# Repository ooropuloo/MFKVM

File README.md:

# MF KVM

**繁體中文** | [English](README.en.md)

MF KVM 是以 ESP32-P4 為主控、跑 [ESP-KVM](https://github.com/espkvm/espkvm) 韌體的 KVM over IP 小盒子：接上主機的 HDMI 和 USB 之後，就能透過 Wi-Fi 從瀏覽器看主機畫面、操作鍵盤滑鼠，也能按主機的電源和重置鍵。這個 repo 並列兩個設計：`off-the-shelf/` 用買得到的現成板組裝，只自製一片 ATX 小板；`lay-board/` 把所有電路自己布在一片 6 層板上。

**狀態：還沒有做出實品。** 目前版本 r7f 已送 JLC 審核、尚未付款。通過的都是檔案和模型層級的檢查，沒有任何一項在硬體上驗證過。

授權見 [LICENSE](LICENSE)：硬體 CERN-OHL-P-2.0、程式 Apache-2.0、文件 CC-BY-4.0。第三方內容另依原本的條款，見 [THIRD_PARTY.md](THIRD_PARTY.md)。

## 目前版本：r7f

6 層單片板，雙面放零件。主控是 ESP32-P4-Module（U1，組裝後手焊），影像用 TC358743（U7，BGA）。

| 正面 | 背面 |
|---|---|
|  |  |

<details>
<summary>零件代號對照表（點開看圖查詢）</summary>

**正面（Top）**

| 代號 | 是什麼 | 用途／備註 |
|---|---|---|
| U1 | ESP32-P4 模組 | 主控加 Wi-Fi，客供、組裝後手焊，最大熱源 |
| J3 | USB-C | 接被控主機（鍵盤滑鼠、虛擬媒體） |
| J5 | USB-C | 5 V 供電、燒錄、console |
| J6 | SM08B 8P | 接圓形 LCD |
| U14 | ESD 保護 | J5 的 USB 線 |
| U15 + L2 | 降壓 | 3V3 → 1.2 V |
| D1 | ESD 保護 | HDMI CEC |

**背面（Bottom）**

| 代號 | 是什麼 | 用途／備註 |
|---|---|---|
| J2 | HDMI | 影像輸入 |
| U7 | TC358743 BGA | HDMI 轉 CSI，最燙的晶片 |
| J7 | microSD | 虛擬媒體、儲存 |
| U16 | TPS259531 eFuse | 5 V 輸入保護，下單要核對方向 |
| U2 + L1 | 降壓 | 5 V → 3V3 |
| U4 | LDO | 3V3 → 2.5 V |
| U6 | TCA9517A | HDMI DDC 準位轉換 |
| U3、U8、U9 | ESD 保護 | J3 的 USB 線、HDMI TMDS |
| U10、U11、U12 | 光耦 | ATX 電源、重置、LED |
| J4 | SM06B 6P | 接 ATX 前面板 |
| J8 | U.FL | 接 Wi-Fi 天線 |
| Y1 | 27 MHz 振盪器 | U7 的時脈 |
| Q1 | P 通道 MOSFET | microSD 電源開關 |
| C69 | 330 µF POSCAP | 5 V 大電容 |

電阻、電容太多沒有列，完整清單見 [`BOM_JLC.csv`](lay-board/r7f/fab_r7f/BOM_JLC.csv)。

</details>

| 外殼組裝 | 爆炸圖 |
|---|---|
|  |  |

以上都是電腦算繪，不是照片。板檔沒有 3D 模型，零件是依外形和高度畫的方塊，風扇是示意外形。

| 項目 | 規格 |
|---|---|
| 板子 | 40 × 45 mm，6 層，JLC06121H-3313 |
| 外殼本體 | 44 × 49 × 20 mm，鋁上蓋，底殼 ASA／ABS／PC／PA12（不用 PLA） |
| 含導管和風扇 | 44 × 69.2 × 35 mm（風扇厚度 10 mm 是假設） |
| 額定環境溫度 | 25 °C，要裝導管式風扇 |
| 主控 | ESP32-P4-Module 基本款（SKU 28101），內建 ESP32-C6，2.4 GHz Wi-Fi，U.FL 外接天線 |
| 影像 | TC358743XBG，HDMI 轉 CSI |
| 螢幕 | 1.28 吋圓形 LCD |
| 打板包 | [`lay-board/r7f/fab_r7f/`](lay-board/r7f/fab_r7f/)，Gerber zip sha256 開頭 `5edbd116` |

### 這版改了什麼（相對 r7e）

下表的數字都是模型算出來的，不是實測。

| 項目 | 改了什麼 | 結果 |
|---|---|---|
| 5 V 輸入保護 | 加 eFuse U16（TPS259531），限流約 2 A，輸出鉗位 5.7 V | 插電瞬間峰值電流 10–18 A → 4.1–5.3 A |
| HDMI CEC | CEC 線加 ESD 保護 D1（TPD1E10B06） | 原本這條線沒有保護 |
| microSD 訊號 | 6 條線各串 22 Ω（R74–R79） | 寫入過衝 0.79–1.16 V → 0.05–0.23 V |
| LCD 訊號 | DIN、CLK 串 33 Ω（R80、R81，0201） | LCD CLK 過衝 1.51 V → 0.61 V |
| 散熱 | 鋁上蓋、0.8 mm 鋁板、P4 和 C6 上的導熱膠、12 條通風槽 | 一般負載下上蓋 52.9 °C → 49.5 °C（環境 25 °C） |
| 導管式風扇 | 加 3D 列印導管和 30 mm 風扇，風扇自己接 USB 供電，PCB 不改 | 上蓋 36.2 °C、底殼 41.5 °C，低於接觸超過 1 分鐘的 48 °C（0.15 L/s，流量是假設） |
| 外殼接地 | 安裝孔鍍通接地，上蓋和鋁板的接觸面不上陽極膜 | 驗收：上蓋、鋁板對 GND 要 < 1 Ω |
| 手焊間距 | U1 旁 22 個焊盤都留 ≥ 0.2 mm 和防焊隔開，J6 外移 0.65 mm | 最小 0.387 mm |

**從 r5 走到 r7f 的主要變化：** r6 加 U.FL 和 50 Ω RF 線、阻抗改用場解算；r7 的 1.2 V 改成降壓（U15）、DDC 改 TCA9517A；r7c 板子加長到 40 × 45 mm 並加 C69；r7d 做 CSI 等長；r7e 補冷啟動分析。

### 驗證到哪裡

| 已通過（檔案和模型層級） | 結果 |
|---|---|
| ERC、DRC | 0 錯誤、0 未連線，29 個警告逐項接受 |
| 電氣規則檢查（含 eFuse） | 全部通過 |
| 故意放錯測試 | 126 次全部抓到 |
| 外殼幾何 | 99/99 |
| 阻抗、CSI 等長、參考層、防焊、孔距、零件本體 | 通過 |
| 獨立複審與差異複審 | 0 嚴重，有條件可送板 |

**沒有驗證：** 還沒有實體板，EMI、RF／RSSI、影像、USB、Wi-Fi、風扇實際風量和溫度都沒測過。完整清單在[驗證報告](lay-board/r7f/pdf/r7f_驗證報告.pdf)第 2 節。

**現在的進度：** 已送 JLC 審核，尚未付款，尚未打板。JLC 按確認前還要在預覽逐顆核對 U16 第 1 腳和 16 顆方向未定的零件（U16 轉 180° 會讓 VBUS 短路到 GND）。

**完整資料：** [r7f 說明](lay-board/r7f/README.md)、[改版報告](lay-board/r7f/R7F_REPORT.md)、[獨立複審](lay-board/r7f/REVIEW_r7f.md)、[差異複審](lay-board/r7f/DELTA_r7f.md)、[圖面與報告 PDF](lay-board/r7f/pdf/)。

## 較早的設計（ARCHIVE）

以下保留當時的內容當紀錄，都不是目前版本。`lay-board/` 這欄是 r5，那張單已經取消。

| | [`off-the-shelf/`](off-the-shelf/README.md)（現成料，第三版） | [`lay-board/`](lay-board/README.md)（客製板，第二版 r5） |
|---|---|---|
| **外殼尺寸** | 75.0 × 38.05 × 26.73 mm | 44 × 44 × 20 mm |
| **體積** | 76 cm³ | 39 cm³ |
| **買什麼** | DFRobot FireBeetle 2 ESP32-P4（DFR1172）、Geekworm C790、Waveshare 1.9 吋 LCD、Würth 50 mm 15-pin 排線（接點異面、同面各 1）、改過不接 VBUS 的 USB 線、Ø0.64 銅線、JST SH 線、螺絲、5 V 電源 | Waveshare ESP32-P4-Module-U（IPEX）、FPC 天線、1.28 吋圓形 LCD、自製 SHR-08 和 SHR-06 線、M2 × 16 螺絲 4 支 |
| **打什麼板** | 2 層 ATX 小板 rev B，11.05 × 35.4 mm（`fab_atx_b/`），尚未下單 | 6 層 40 × 40 mm 主板加雙面 PCBA，含 BGA（`fab_r5/`），JLC 審查中、未付款 |
| **印什麼** | 底殼、上蓋、C790 橋架、排線捲線棒、ATX 焊接墊片（建議 PETG） | 底殼、上蓋 |
| **韌體** | ESP-KVM `0893eef`，加 ST7789 修補與 ATX 修補（兩支 patch），只編譯過 | ESP-KVM `0893eef`，加開機預設值修補與 ATX 修補（兩支 patch），只編譯過。ATX 預設關閉，到 console 打開，見 `lay-board/firmware/BUILD_v2.md` |
| **主要風險** | 排線斜捲 45° 沒人測過、回報僅約 9 fps、ATX 小板焊死後要斜著裝 | 首版 6 層加 BGA 有錯就要重打、阻抗只有公式估算、最壞公差有 4 對本體可能相碰 |
| **狀態** | 只有設計，零件未買 | 打板包只能送 CAM 預審，還不能算放行 |
| **什麼時候選它** | 想先驗證功能、不想打 6 層板和焊 BGA、接受比較大的盒子。目前建議當驗證機，也能先驗證兩邊共用的韌體 | 要最小的外形，或要走正式小型產品，且願意承擔首版改板 |

每個設計的 README 都有 **「還缺什麼」** 清單，列出下單前和實機要做的事：[off-the-shelf](off-the-shelf/README.md#還缺什麼)、[lay-board](lay-board/README.md#還缺什麼)。

## 當時的建議順序（r5 時期）

1. 買 `off-the-shelf` 的料，先用線接起來跑通影像、USB、Wi-Fi，不用打板也不用列印。
2. 拿實測影格率決定 `off-the-shelf` 能不能接受，同時驗證 `lay-board` 也會用到的韌體路徑。
3. `lay-board` 依 CAM 回覆決定要不要修，審查通過也先不付款，全部驗證過才打板。

## 3D 頁面

這兩個連結是**擁有者私人頁面，別人打不開**。每個資料夾裡的本機 HTML 是同一份內容，下載後用瀏覽器開就能看（3D 需要連上網路載入 three.js）：

| 設計 | 私人連結 | 本機檔案 |
|---|---|---|
| lay-board | https://claude.ai/artifact/GMou6HJAjchfPkJ2fzq8we | [`lay-board/kvm-mini.html`](lay-board/kvm-mini.html) |
| off-the-shelf | https://claude.ai/artifact/LdwRVth9BPiBVDjdgMhgdb | [`off-the-shelf/v3.html`](off-the-shelf/v3.html) |

## 不在這個 repo 的東西

- **第一版（NANO 模組疊自製底板）：** 排針位置錯，已放棄，沒有放進來。
- **舊打板包：** `fab`、`fab_new`、`fab_r2`～`fab_r4`、`fab_atx` 都不能用，原因寫在各 README。
- **建置輸出：** ESP-KVM clone、build 目錄、映像檔、建置 log。重新編譯的方法在各 README。
- **第三方原始檔：** NANO 官方 CAD、ExoAnchor 壓縮檔、FireBeetle STEP。來源見 [THIRD_PARTY.md](THIRD_PARTY.md) 和 `off-the-shelf/research/`。

## 常用檢查（在 repo 根目錄）

```sh
python lay-board/tools/maskcheck.py lay-board/fab_r5/p4_kvm_mini_gerber.zip
python lay-board/tools/holecheck.py lay-board/fab_r5/p4_kvm_mini_gerber.zip
sh lay-board/tools/check.sh out/final.ses     # 要 KiCad，路徑用 KICAD_CLI、KICAD_TOOL_HOME 覆寫
python lay-board/tools/bodycheck.py lay-board/out
python lay-board/tools/maskcheck.py off-the-shelf/fab_atx_b/mf_kvm_atx_gerber.zip
python lay-board/tools/holecheck.py off-the-shelf/fab_atx_b/mf_kvm_atx_gerber.zip
```

`.gitattributes` 設定 `* -text`，檔案逐位元組保存，不轉換行尾，所以 Gerber 雜湊不會變，`.sh` 也不會變成 CRLF。

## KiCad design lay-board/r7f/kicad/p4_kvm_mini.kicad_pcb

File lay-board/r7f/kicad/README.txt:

r7b design files, copied from out/ after the final check (board sha256 2acf1c0fcd2acbffd97f6878b55f344319c8f6496172503f295ab0cfc3b03e46).
They are the files fab_r7b/ was made from. Regenerate with gen_mini.py; do not edit these by hand.

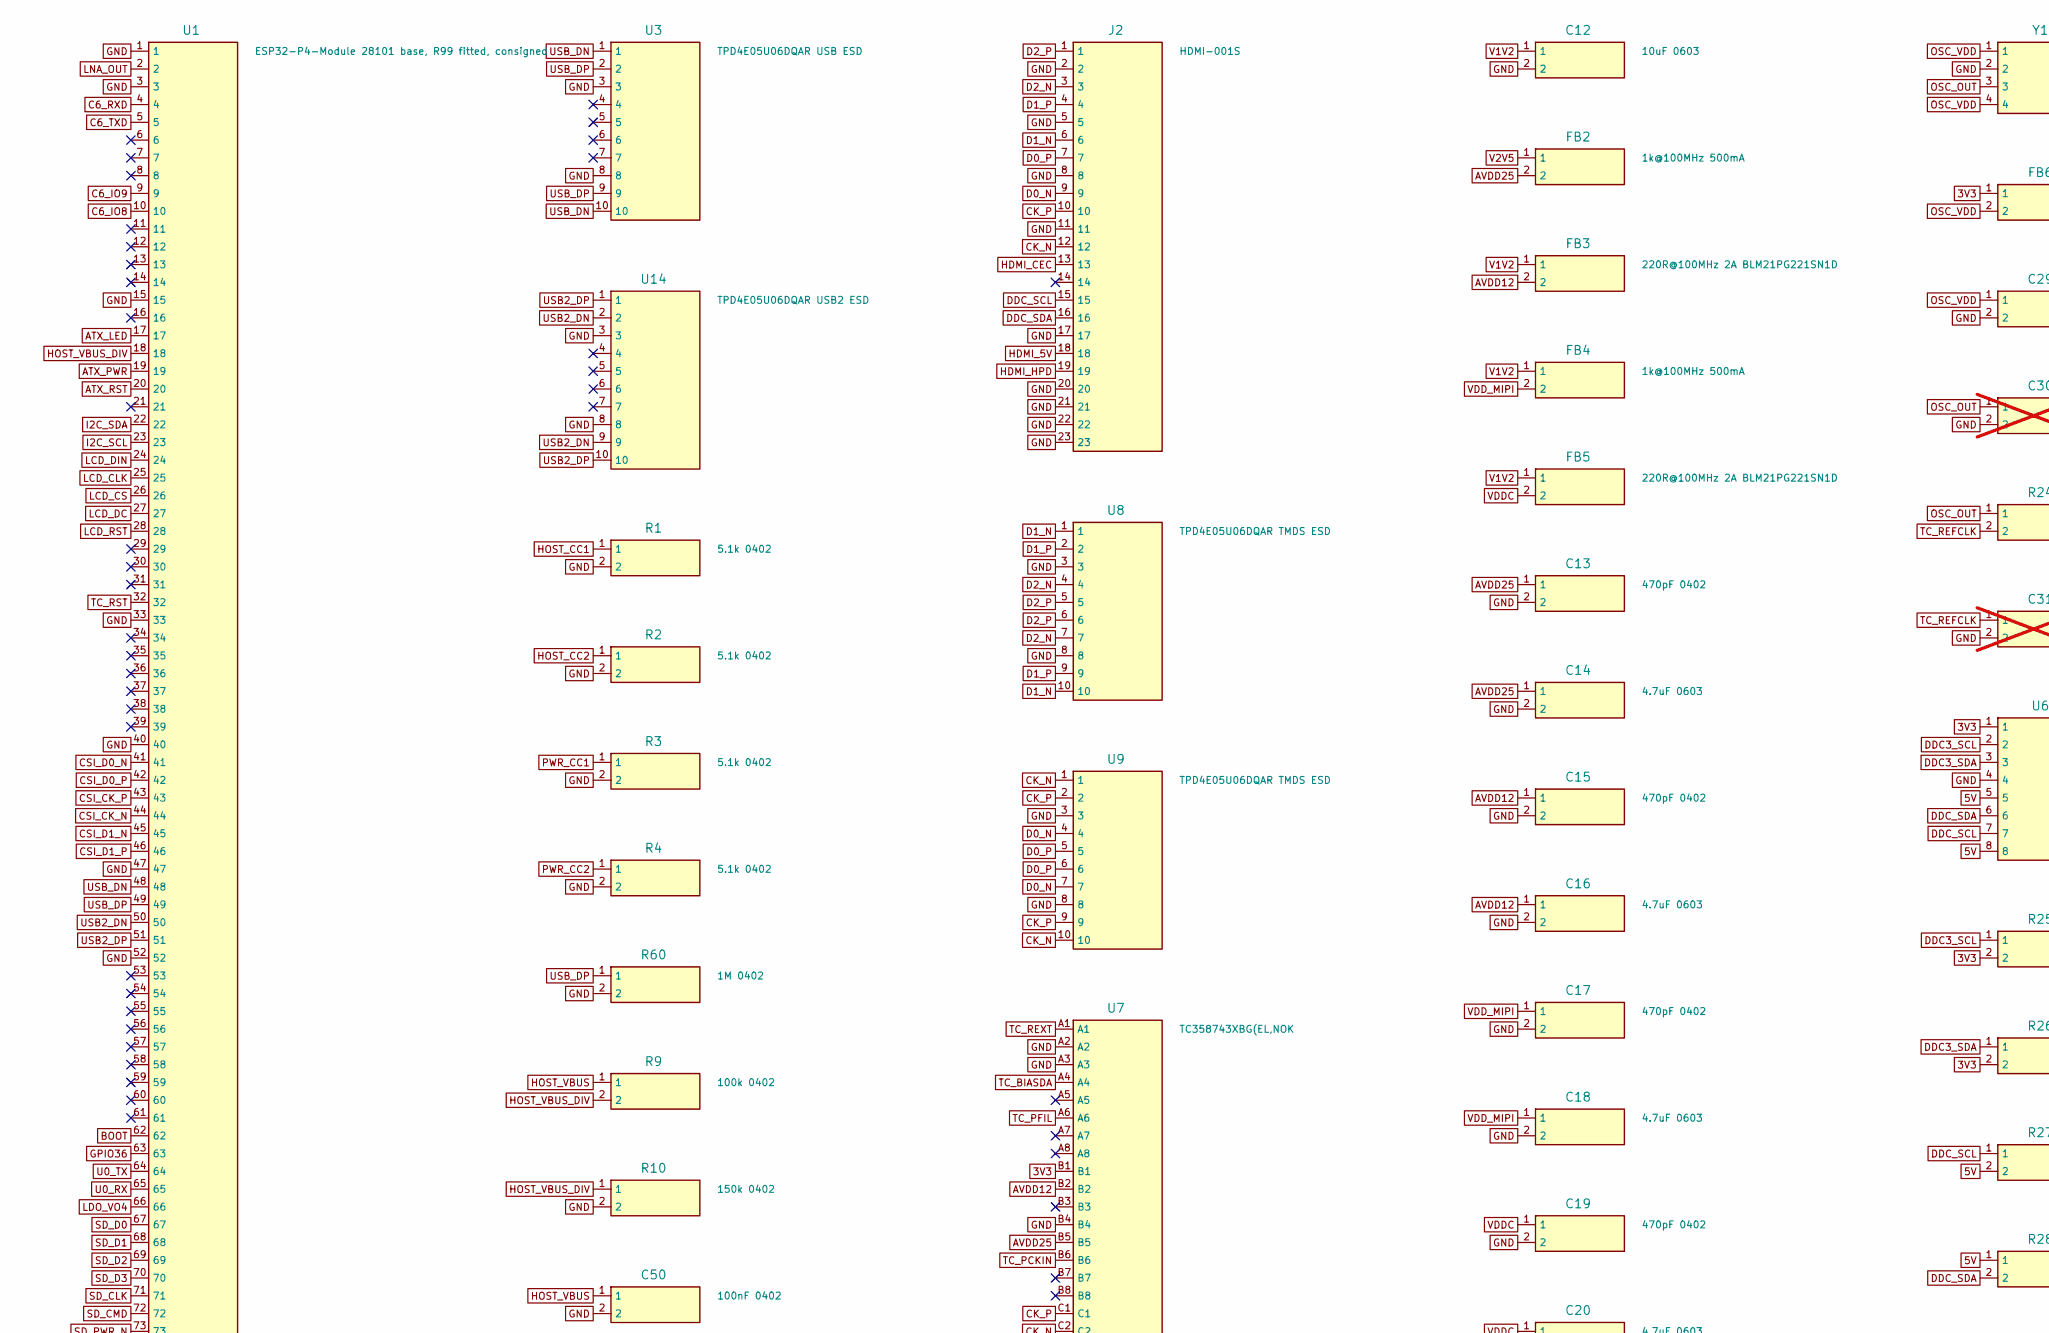
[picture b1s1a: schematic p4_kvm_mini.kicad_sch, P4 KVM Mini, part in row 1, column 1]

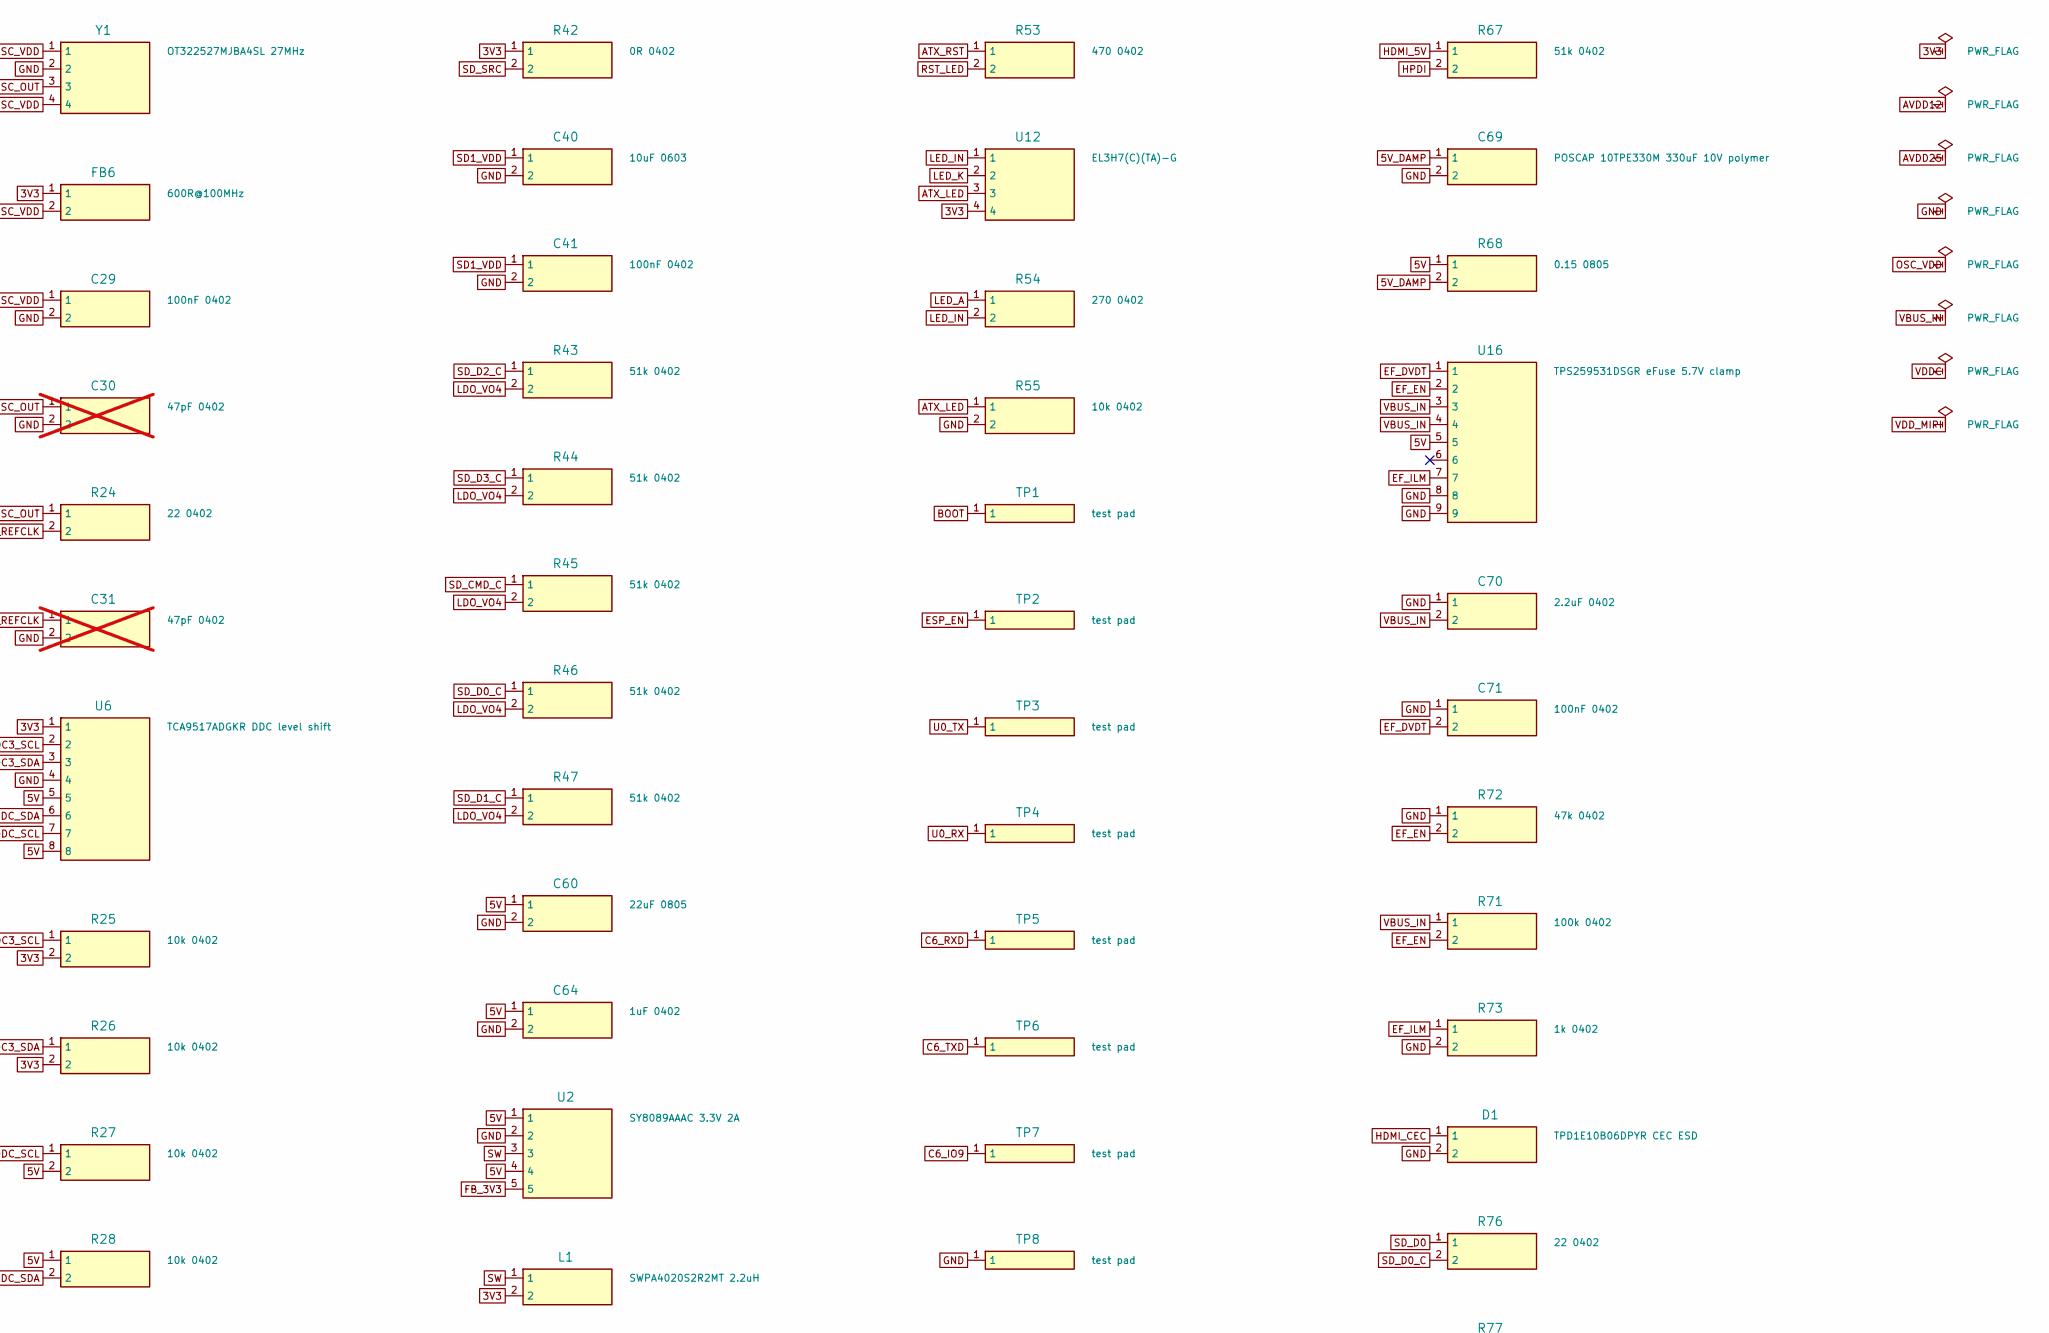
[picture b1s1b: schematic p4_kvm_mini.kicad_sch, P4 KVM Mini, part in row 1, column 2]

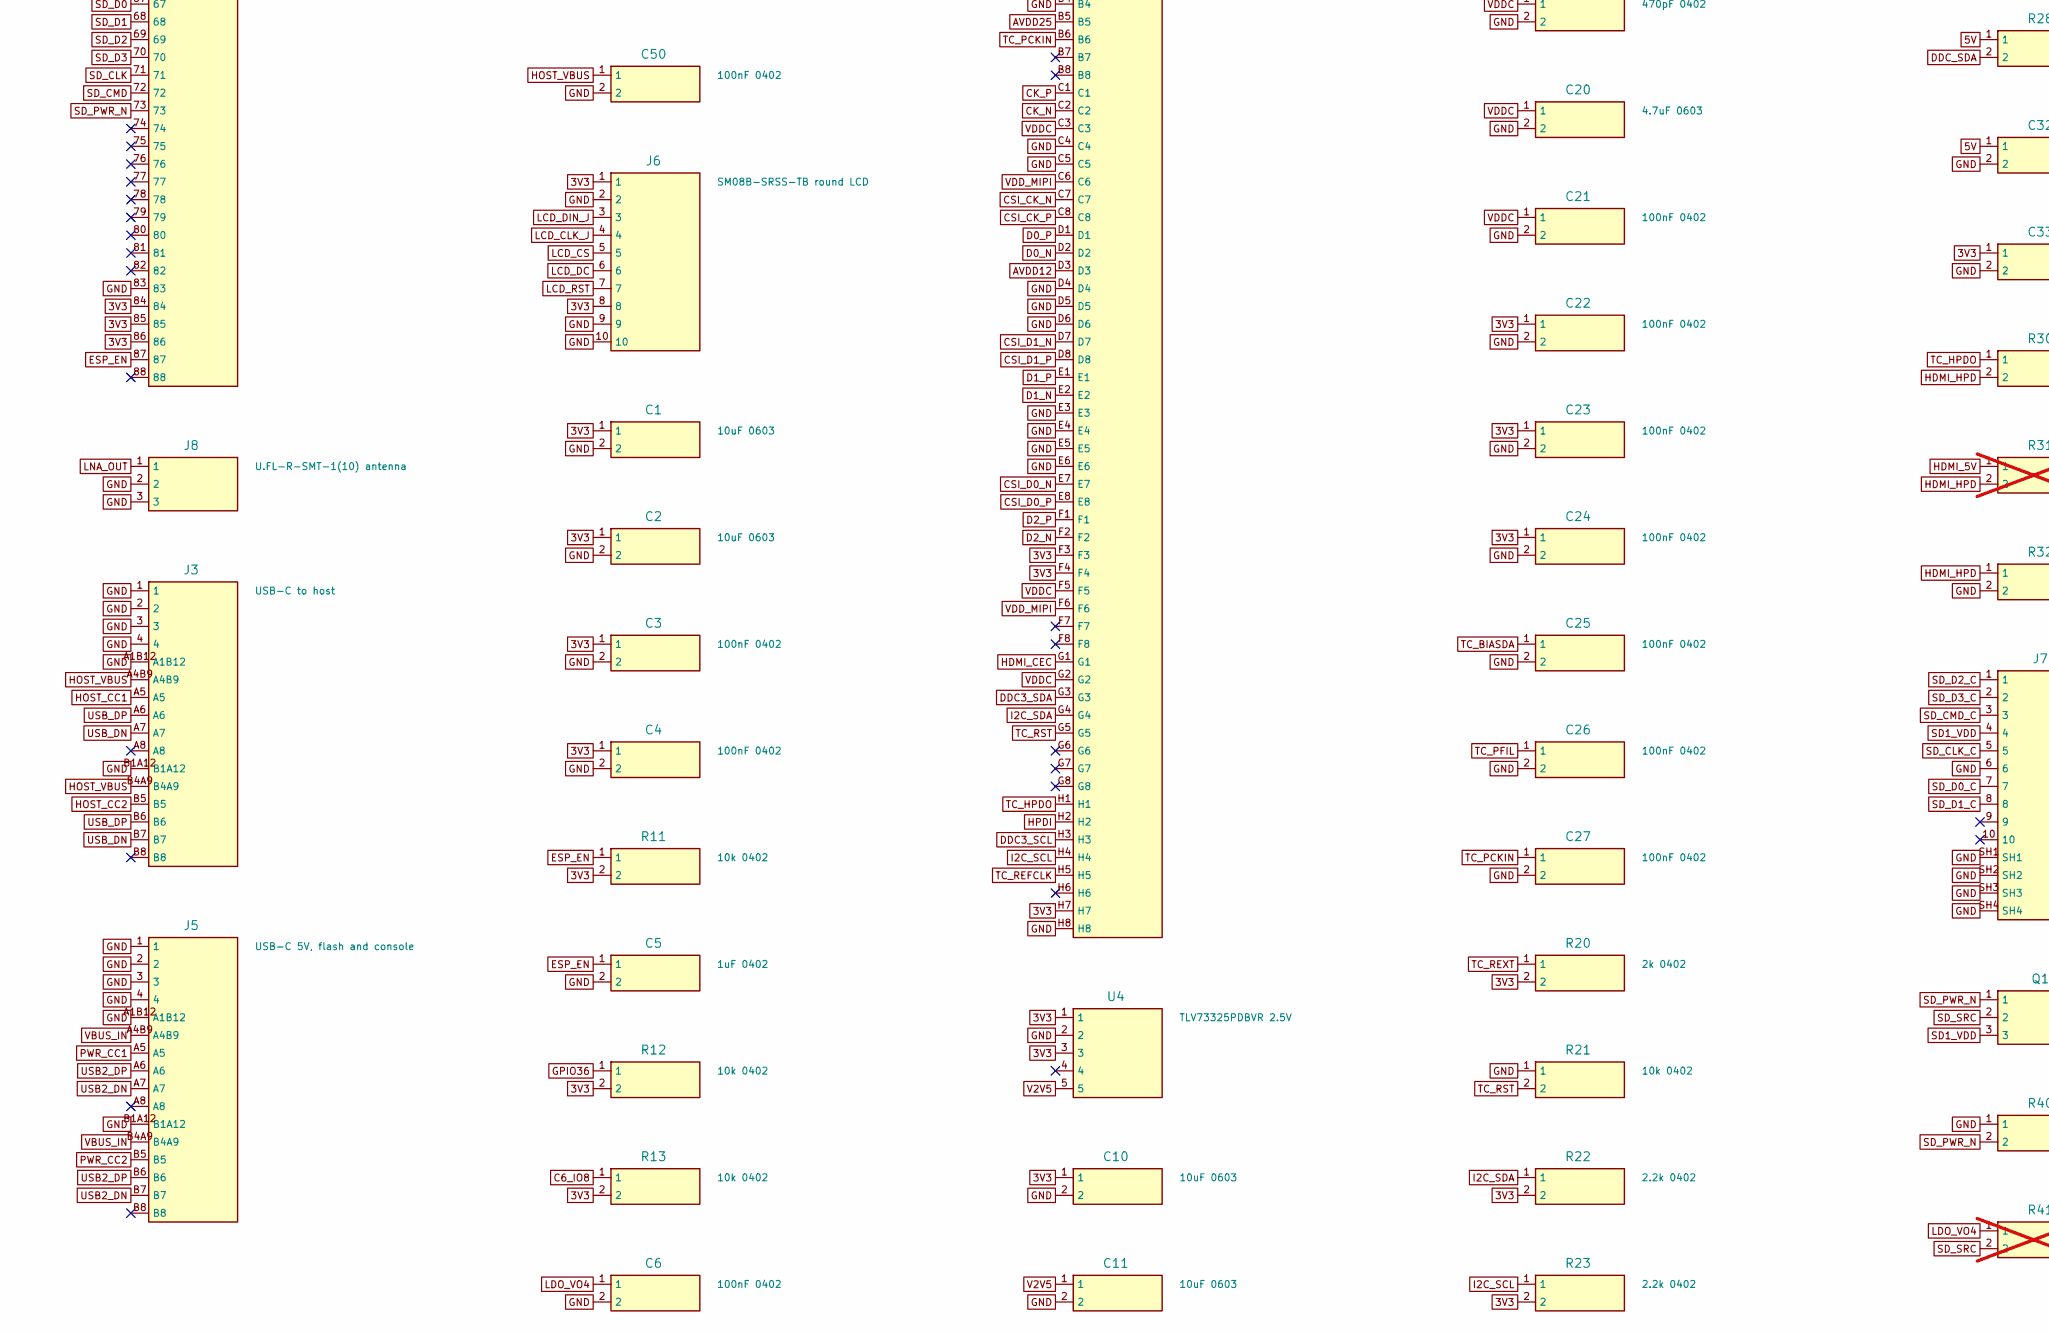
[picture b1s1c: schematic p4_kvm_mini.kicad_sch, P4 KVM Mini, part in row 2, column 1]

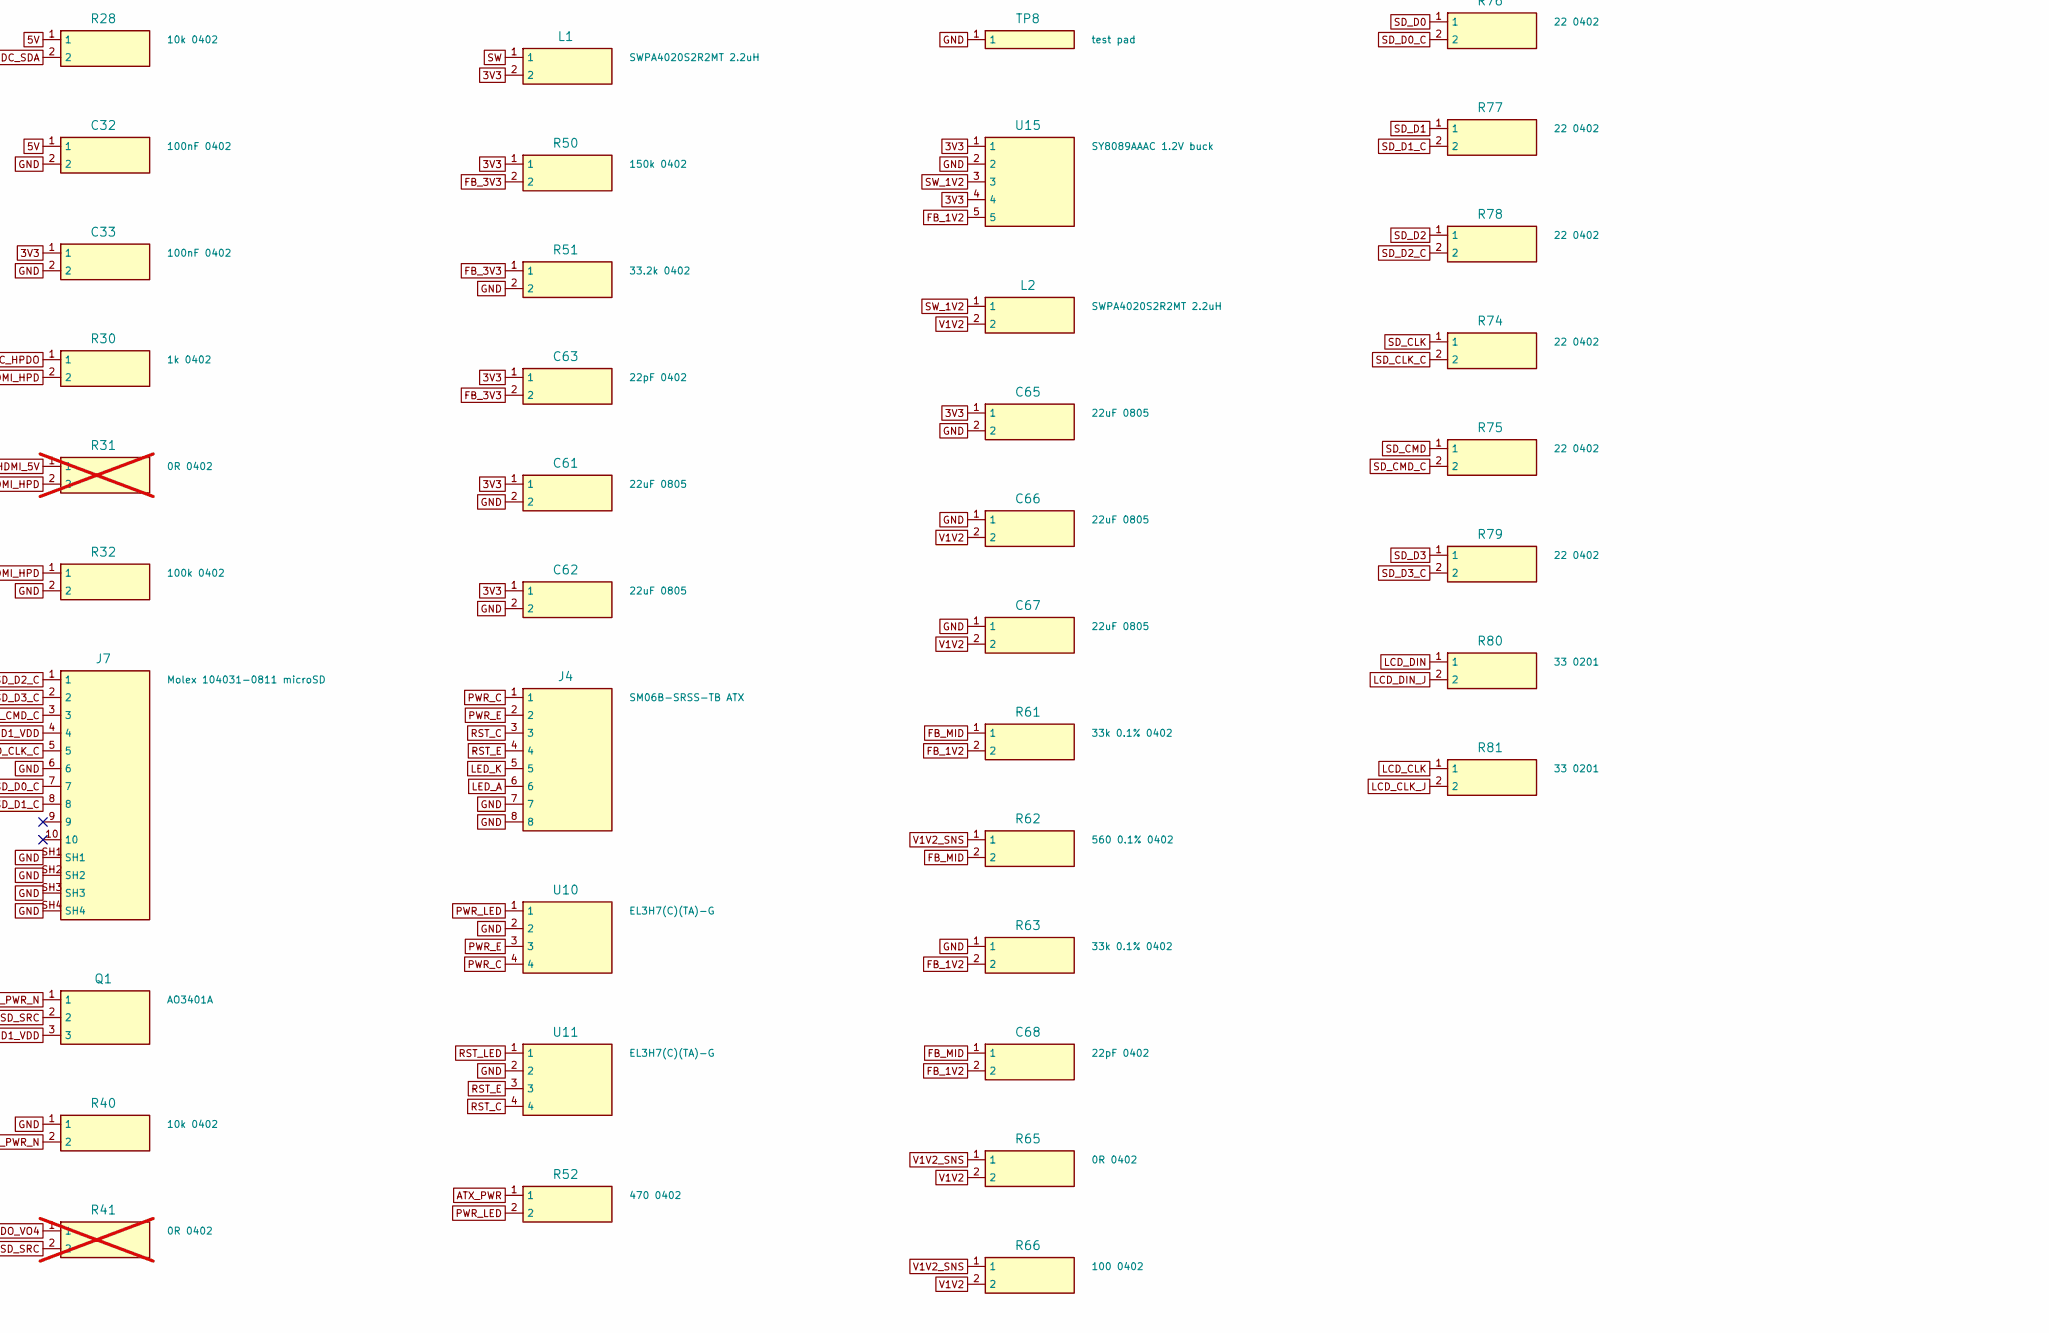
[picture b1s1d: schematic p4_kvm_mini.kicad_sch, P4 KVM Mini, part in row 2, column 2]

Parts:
C1, C2, C10, C11, C12, C40: 10uF 0603; C0603; LCSC C19702
C3, C4, C6, C21, C22, C23, C24, C25, C26, C27, C29, C32, C33, C41, C50, C71: 100nF 0402; R0402; LCSC C1525
C5, C64: 1uF 0402; R0402; LCSC C52923
C13, C15, C17, C19: 470pF 0402; R0402; LCSC C1537
C14, C16, C18, C20: 4.7uF 0603; C0603; LCSC C19666
C30, C31: 47pF 0402; R0402; LCSC C1567; not fitted
C60, C61, C62, C65, C66, C67: 22uF 0805; C0805; LCSC C45783
C63, C68: 22pF 0402; R0402; LCSC C1555
C69: POSCAP 10TPE330M 330uF 10V polymer; CP_7343; LCSC C347552
C70: 2.2uF 0402; R0402; LCSC C385032
D1: TPD1E10B06DPYR CEC ESD; X1SON-2_0.6x1; LCSC C48260
FB2, FB4: 1k@100MHz 500mA; C0805; LCSC C98485
FB3, FB5: 220R@100MHz 2A BLM21PG221SN1D; C0805; LCSC C85840
FB6: 600R@100MHz; C0603; LCSC C19330
J2: HDMI-001S; LCSC C720616
J3: USB-C to host; USB-C_HX_16P; LCSC C41427493
J4: SM06B-SRSS-TB ATX; JST_SM06B; LCSC C160405
J5: USB-C 5V, flash and console; USB-C_HX_16P; LCSC C41427493
J6: SM08B-SRSS-TB round LCD; JST_SM08B; LCSC C160407
J7: Molex 104031-0811 microSD; microSD_Molex_104031-0811; LCSC C585350
J8: U.FL-R-SMT-1(10) antenna; U.FL-R-SMT-1; LCSC C88373
L1, L2: SWPA4020S2R2MT 2.2uH; IND4020; LCSC C83423
Q1: AO3401A; SOT-23; LCSC C15127
R1, R2, R3, R4: 5.1k 0402; R0402; LCSC C25905
R9, R32, R71: 100k 0402; R0402; LCSC C25741
R10, R50: 150k 0402; R0402; LCSC C25755
R11, R12, R13, R21, R25, R26, R27, R28, R40, R55: 10k 0402; R0402; LCSC C25744
R20: 2k 0402; R0402; LCSC C4109
R22, R23: 2.2k 0402; R0402; LCSC C25879
R24, R74, R75, R76, R77, R78, R79: 22 0402; R0402; LCSC C25092
R30, R73: 1k 0402; R0402; LCSC C11702
R31, R41: 0R 0402; R0402; LCSC C17168; not fitted
R42, R65: 0R 0402; R0402; LCSC C17168
R43, R44, R45, R46, R47, R67: 51k 0402; R0402; LCSC C25794
R51: 33.2k 0402; R0402; LCSC C122548
R52, R53: 470 0402; R0402; LCSC C25117
R54: 270 0402; R0402; LCSC C25099
R60: 1M 0402; R0402; LCSC C26083
R61, R63: 33k 0.1% 0402; R0402; LCSC C728559
R62: 560 0.1% 0402; R0402; LCSC C319512
R66: 100 0402; R0402; LCSC C25076
R68: 0.15 0805; C0805; LCSC C247444
R72: 47k 0402; R0402; LCSC C25792
R80, R81: 33 0201; R0201; LCSC C320843
TP1, TP2, TP3, TP4, TP5, TP6, TP7, TP8: test pad; TP_1.0
U1: ESP32-P4-Module 28101 base, R99 fitted, consigned; ESP32-P4-Module
U2: SY8089AAAC 3.3V 2A; SOT-23-5; LCSC C78988
U3: TPD4E05U06DQAR USB ESD; USON-10; LCSC C138714
U4: TLV73325PDBVR 2.5V; SOT-23-5; LCSC C882825
U6: TCA9517ADGKR DDC level shift; MSOP-8; LCSC C201698
U7: TC358743XBG(EL,NOK; BGA-64_6x6; LCSC C3008606
U8, U9: TPD4E05U06DQAR TMDS ESD; USON-10; LCSC C138714
U10, U11, U12: EL3H7(C)(TA)-G; SSOP-4_1.27; LCSC C92243
U14: TPD4E05U06DQAR USB2 ESD; USON-10; LCSC C138714
U15: SY8089AAAC 1.2V buck; SOT-23-5; LCSC C78988
U16: TPS259531DSGR eFuse 5.7V clamp; WSON-8_2x2_EP; LCSC C2155674
Y1: OT322527MJBA4SL 27MHz; OSC3225; LCSC C725995

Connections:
3V3: C1.1, C2.1, C3.1, C4.1, C10.1, C22.1, C23.1, C24.1, C33.1, C61.1, C62.1, C63.1, C65.1, FB6.1, J6.1, J6.8, L1.2, R11.2, R12.2, R13.2, R20.2, R22.2, R23.2, R25.2, R26.2, R42.1, R50.1, U1.84, U1.85, U1.86, U4.1, U4.3, U6.1, U7.B1, U7.F3, U7.F4, U7.H7, U12.4, U15.1, U15.4
5V: C32.1, C60.1, C64.1, R27.2, R28.1, R68.1, U2.1, U2.4, U6.5, U6.8, U16.5
5V_DAMP: C69.1, R68.2
ATX_LED: R55.1, U1.17, U12.3
ATX_PWR: R52.1, U1.19
ATX_RST: R53.1, U1.20
AVDD12: C15.1, C16.1, FB3.2, U7.B2, U7.D3
AVDD25: C13.1, C14.1, FB2.2, U7.B5
BOOT: TP1.1, U1.62
C6_IO8: R13.1, U1.10
C6_IO9: TP7.1, U1.9
C6_RXD: TP5.1, U1.4
C6_TXD: TP6.1, U1.5
CK_N: J2.12, U7.C2, U9.1, U9.10
CK_P: J2.10, U7.C1, U9.2, U9.9
CSI_CK_N: U1.44, U7.C7
CSI_CK_P: U1.43, U7.C8
CSI_D0_N: U1.41, U7.E7
CSI_D0_P: U1.42, U7.E8
CSI_D1_N: U1.45, U7.D7
CSI_D1_P: U1.46, U7.D8
D0_N: J2.9, U7.D2, U9.4, U9.7
D0_P: J2.7, U7.D1, U9.5, U9.6
D1_N: J2.6, U7.E2, U8.1, U8.10
D1_P: J2.4, U7.E1, U8.2, U8.9
D2_N: J2.3, U7.F2, U8.4, U8.7
D2_P: J2.1, U7.F1, U8.5, U8.6
DDC3_SCL: R25.1, U6.2, U7.H3
DDC3_SDA: R26.1, U6.3, U7.G3
DDC_SCL: J2.15, R27.1, U6.7
DDC_SDA: J2.16, R28.2, U6.6
EF_DVDT: C71.2, U16.1
EF_EN: R71.2, R72.2, U16.2
EF_ILM: R73.1, U16.7
ESP_EN: C5.1, R11.1, TP2.1, U1.87
FB_1V2: C68.2, R61.2, R63.2, U15.5
FB_3V3: C63.2, R50.2, R51.1, U2.5
FB_MID: C68.1, R61.1, R62.2
GND: C1.2, C2.2, C3.2, C4.2, C5.2, C6.2, C10.2, C11.2, C12.2, C13.2, C14.2, C15.2, C16.2, C17.2, C18.2, C19.2, C20.2, C21.2, C22.2, C23.2, C24.2, C25.2, C26.2, C27.2, C29.2, C30.2, C31.2, C32.2, C33.2, C40.2, C41.2, C50.2, C60.2, C61.2, C62.2, C64.2, C65.2, C66.1, C67.1, C69.2, C70.1, C71.1, D1.2, J2.2, J2.5, J2.8, J2.11, J2.17, J2.20, J2.21, J2.22, J2.23, J3.1, J3.2, J3.3, J3.4, J3.A1B12, J3.B1A12, J4.7, J4.8, J5.1, J5.2, J5.3, J5.4, J5.A1B12, J5.B1A12, J6.2, J6.9, J6.10, J7.6, J7.SH1, J7.SH2, J7.SH3, J7.SH4, J8.2, J8.3, R1.2, R2.2, R3.2, R4.2, R10.2, R21.1, R32.2, R40.1, R51.2, R55.2, R60.2, R63.1, R72.1, R73.2, TP8.1, U1.1, U1.3, U1.15, U1.33, U1.40, U1.47, U1.52, U1.83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; also elsewhere on the board
GPIO36: R12.1, U1.63
HDMI_5V: J2.18, R31.1, R67.1
HDMI_CEC: D1.1, J2.13, U7.G1
HDMI_HPD: J2.19, R30.2, R31.2, R32.1
HOST_CC1: J3.A5, R1.1
HOST_CC2: J3.B5, R2.1
HOST_VBUS: C50.1, J3.A4B9, J3.B4A9, R9.1
HOST_VBUS_DIV: R9.2, R10.1, U1.18
HPDI: R67.2, U7.H2
I2C_SCL: R23.1, U1.23, U7.H4
I2C_SDA: R22.1, U1.22, U7.G4
LCD_CLK: R81.1, U1.25
LCD_CLK_J: J6.4, R81.2
LCD_CS: J6.5, U1.26
LCD_DC: J6.6, U1.27
LCD_DIN: R80.1, U1.24
LCD_DIN_J: J6.3, R80.2
LCD_RST: J6.7, U1.28
LDO_VO4: C6.1, R41.1, R43.2, R44.2, R45.2, R46.2, R47.2, U1.66
LED_A: J4.6, R54.1
LED_IN: R54.2, U12.1
LED_K: J4.5, U12.2
LNA_OUT: J8.1, U1.2
OSC_OUT: C30.1, R24.1, Y1.3
OSC_VDD: C29.1, FB6.2, Y1.1, Y1.4
PWR_C: J4.1, U10.4
PWR_CC1: J5.A5, R3.1
PWR_CC2: J5.B5, R4.1
PWR_E: J4.2, U10.3
PWR_LED: R52.2, U10.1
RST_C: J4.3, U11.4
RST_E: J4.4, U11.3
RST_LED: R53.2, U11.1
SD1_VDD: C40.1, C41.1, J7.4, Q1.3
SD_CLK: R74.1, U1.71
SD_CLK_C: J7.5, R74.2
SD_CMD: R75.1, U1.72
SD_CMD_C: J7.3, R45.1, R75.2
SD_D0: R76.1, U1.67
SD_D0_C: J7.7, R46.1, R76.2
SD_D1: R77.1, U1.68
SD_D1_C: J7.8, R47.1, R77.2
SD_D2: R78.1, U1.69
SD_D2_C: J7.1, R43.1, R78.2
SD_D3: R79.1, U1.70
SD_D3_C: J7.2, R44.1, R79.2
SD_PWR_N: Q1.1, R40.2, U1.73
SD_SRC: Q1.2, R41.2, R42.2
SW: L1.1, U2.3
SW_1V2: L2.1, U15.3
TC_BIASDA: C25.1, U7.A4
TC_HPDO: R30.1, U7.H1
TC_PCKIN: C27.1, U7.B6
TC_PFIL: C26.1, U7.A6
TC_REFCLK: C31.1, R24.2, U7.H5
TC_REXT: R20.1, U7.A1
TC_RST: R21.2, U1.32, U7.G5
U0_RX: TP4.1, U1.65
U0_TX: TP3.1, U1.64
USB2_DN: J5.A7, J5.B7, U1.50, U14.2, U14.9
USB2_DP: J5.A6, J5.B6, U1.51, U14.1, U14.10
USB_DN: J3.A7, J3.B7, U1.48, U3.1, U3.10
USB_DP: J3.A6, J3.B6, R60.1, U1.49, U3.2, U3.9
V1V2: C12.1, C66.2, C67.2, FB3.1, FB4.1, FB5.1, L2.2, R65.2, R66.2
V1V2_SNS: R62.1, R65.1, R66.1
V2V5: C11.1, FB2.1, U4.5
VBUS_IN: C70.2, J5.A4B9, J5.B4A9, R71.1, U16.3, U16.4
VDDC: C19.1, C20.1, C21.1, FB5.2, U7.C3, U7.F5, U7.G2
VDD_MIPI: C17.1, C18.1, FB4.2, U7.C6, U7.F6

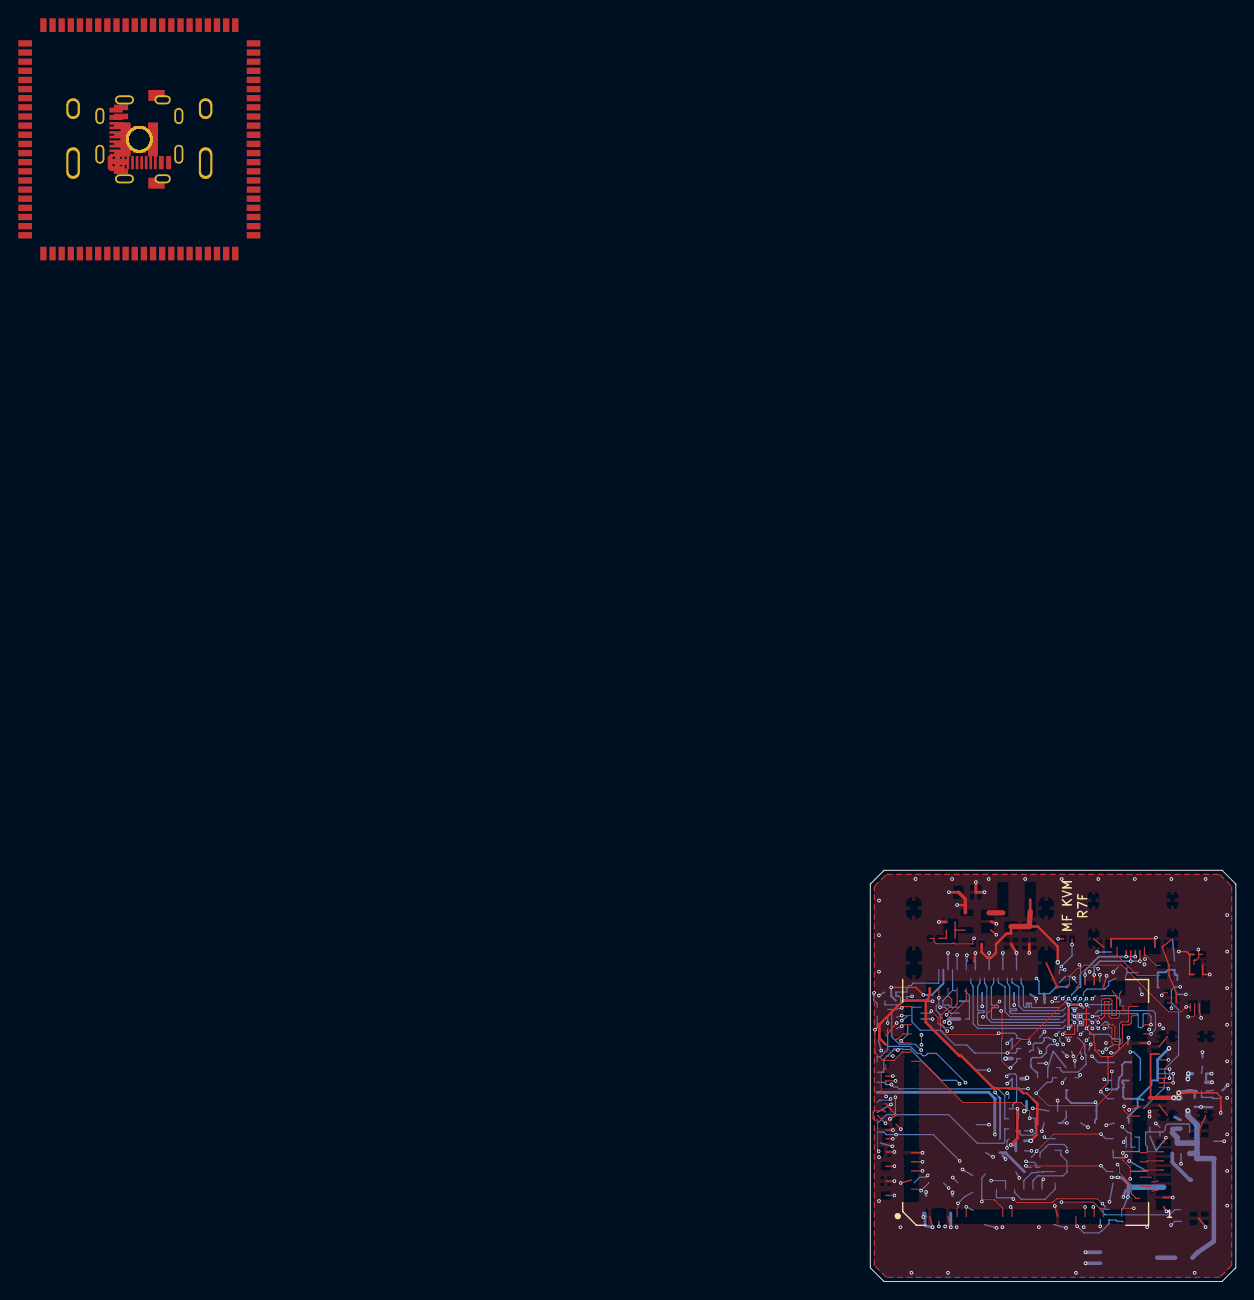
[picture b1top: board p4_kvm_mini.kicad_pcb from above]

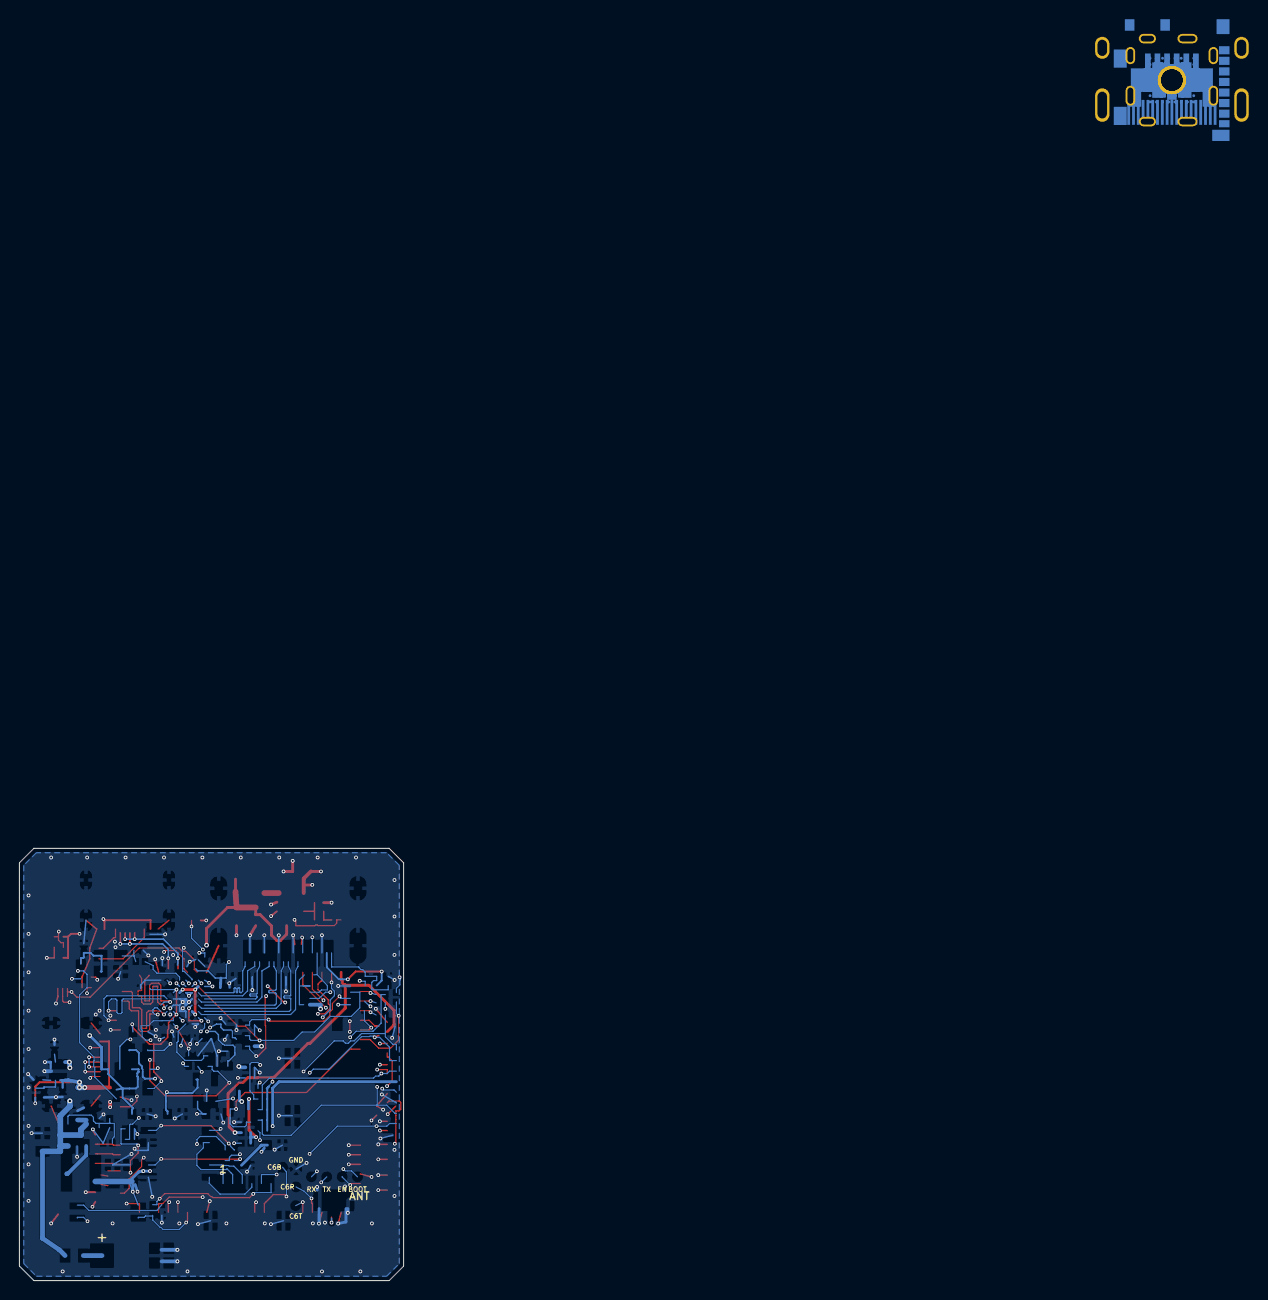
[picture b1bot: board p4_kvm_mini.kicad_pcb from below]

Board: 6 copper layers, 40.0 x 45.0 mm, 141 parts (101 on the bottom side), 108 nets.

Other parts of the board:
H1, H2, H3, H4: MH plated GND; MH_2.2_PTH_GND

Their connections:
GND: H1.1, H2.1, H3.1, H4.1; also elsewhere on the board

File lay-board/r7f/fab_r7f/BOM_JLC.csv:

Comment,Designator,Footprint,LCSC Part #
1k 0402,"R30,R73",R0402,C11702
33.2k 0402,R51,R0402,C122548
TPD4E05U06DQAR USB ESD,U3,USON-10,C138714
TPD4E05U06DQAR USB2 ESD,U14,USON-10,C138714
TPD4E05U06DQAR TMDS ESD,"U8,U9",USON-10,C138714
AO3401A,Q1,SOT-23,C15127
100nF 0402,"C21,C22,C23,C24,C25,C26,C27,C29,C3,C32,C33,C4,C41,C50,C6,C71",R0402,C1525
470pF 0402,"C13,C15,C17,C19",R0402,C1537
22pF 0402,"C63,C68",R0402,C1555
SM06B-SRSS-TB ATX,J4,JST_SM06B,C160405
SM08B-SRSS-TB round LCD,J6,JST_SM08B,C160407
0R 0402,"R42,R65",R0402,C17168
600R@100MHz,FB6,C0603,C19330
4.7uF 0603,"C14,C16,C18,C20",C0603,C19666
10uF 0603,"C1,C10,C11,C12,C2,C40",C0603,C19702
TCA9517ADGKR DDC level shift,U6,MSOP-8,C201698
TPS259531DSGR eFuse 5.7V clamp,U16,WSON-8_2x2_EP,C2155674
0.15 0805,R68,C0805,C247444
100 0402,R66,R0402,C25076
22 0402,"R24,R74,R75,R76,R77,R78,R79",R0402,C25092
270 0402,R54,R0402,C25099
470 0402,"R52,R53",R0402,C25117
100k 0402,"R32,R71,R9",R0402,C25741
10k 0402,"R11,R12,R13,R21,R25,R26,R27,R28,R40,R55",R0402,C25744
150k 0402,"R10,R50",R0402,C25755
47k 0402,R72,R0402,C25792
51k 0402,"R43,R44,R45,R46,R47,R67",R0402,C25794
2.2k 0402,"R22,R23",R0402,C25879
5.1k 0402,"R1,R2,R3,R4",R0402,C25905
1M 0402,R60,R0402,C26083
"TC358743XBG(EL,NOK",U7,BGA-64_6x6,C3008606
560 0.1% 0402,R62,R0402,C319512
33 0201,"R80,R81",R0201,C320843
POSCAP 10TPE330M 330uF 10V polymer,C69,CP_7343,C347552
2.2uF 0402,C70,R0402,C385032
2k 0402,R20,R0402,C4109
USB-C to host,J3,USB-C_HX_16P,C41427493
"USB-C 5V, flash and console",J5,USB-C_HX_16P,C41427493
22uF 0805,"C60,C61,C62,C65,C66,C67",C0805,C45783
TPD1E10B06DPYR CEC ESD,D1,X1SON-2_0.6x1,C48260
1uF 0402,"C5,C64",R0402,C52923
Molex 104031-0811 microSD,J7,microSD_Molex_104031-0811,C585350
HDMI-001S,J2,HDMI-001S,C720616
OT322527MJBA4SL 27MHz,Y1,OSC3225,C725995
33k 0.1% 0402,"R61,R63",R0402,C728559
SY8089AAAC 3.3V 2A,U2,SOT-23-5,C78988
SY8089AAAC 1.2V buck,U15,SOT-23-5,C78988
SWPA4020S2R2MT 2.2uH,"L1,L2",IND4020,C83423
220R@100MHz 2A BLM21PG221SN1D,"FB3,FB5",C0805,C85840
TLV73325PDBVR 2.5V,U4,SOT-23-5,C882825
U.FL-R-SMT-1(10) antenna,J8,U.FL-R-SMT-1,C88373
EL3H7(C)(TA)-G,"U10,U11,U12",SSOP-4_1.27,C92243
1k@100MHz 500mA,"FB2,FB4",C0805,C98485
